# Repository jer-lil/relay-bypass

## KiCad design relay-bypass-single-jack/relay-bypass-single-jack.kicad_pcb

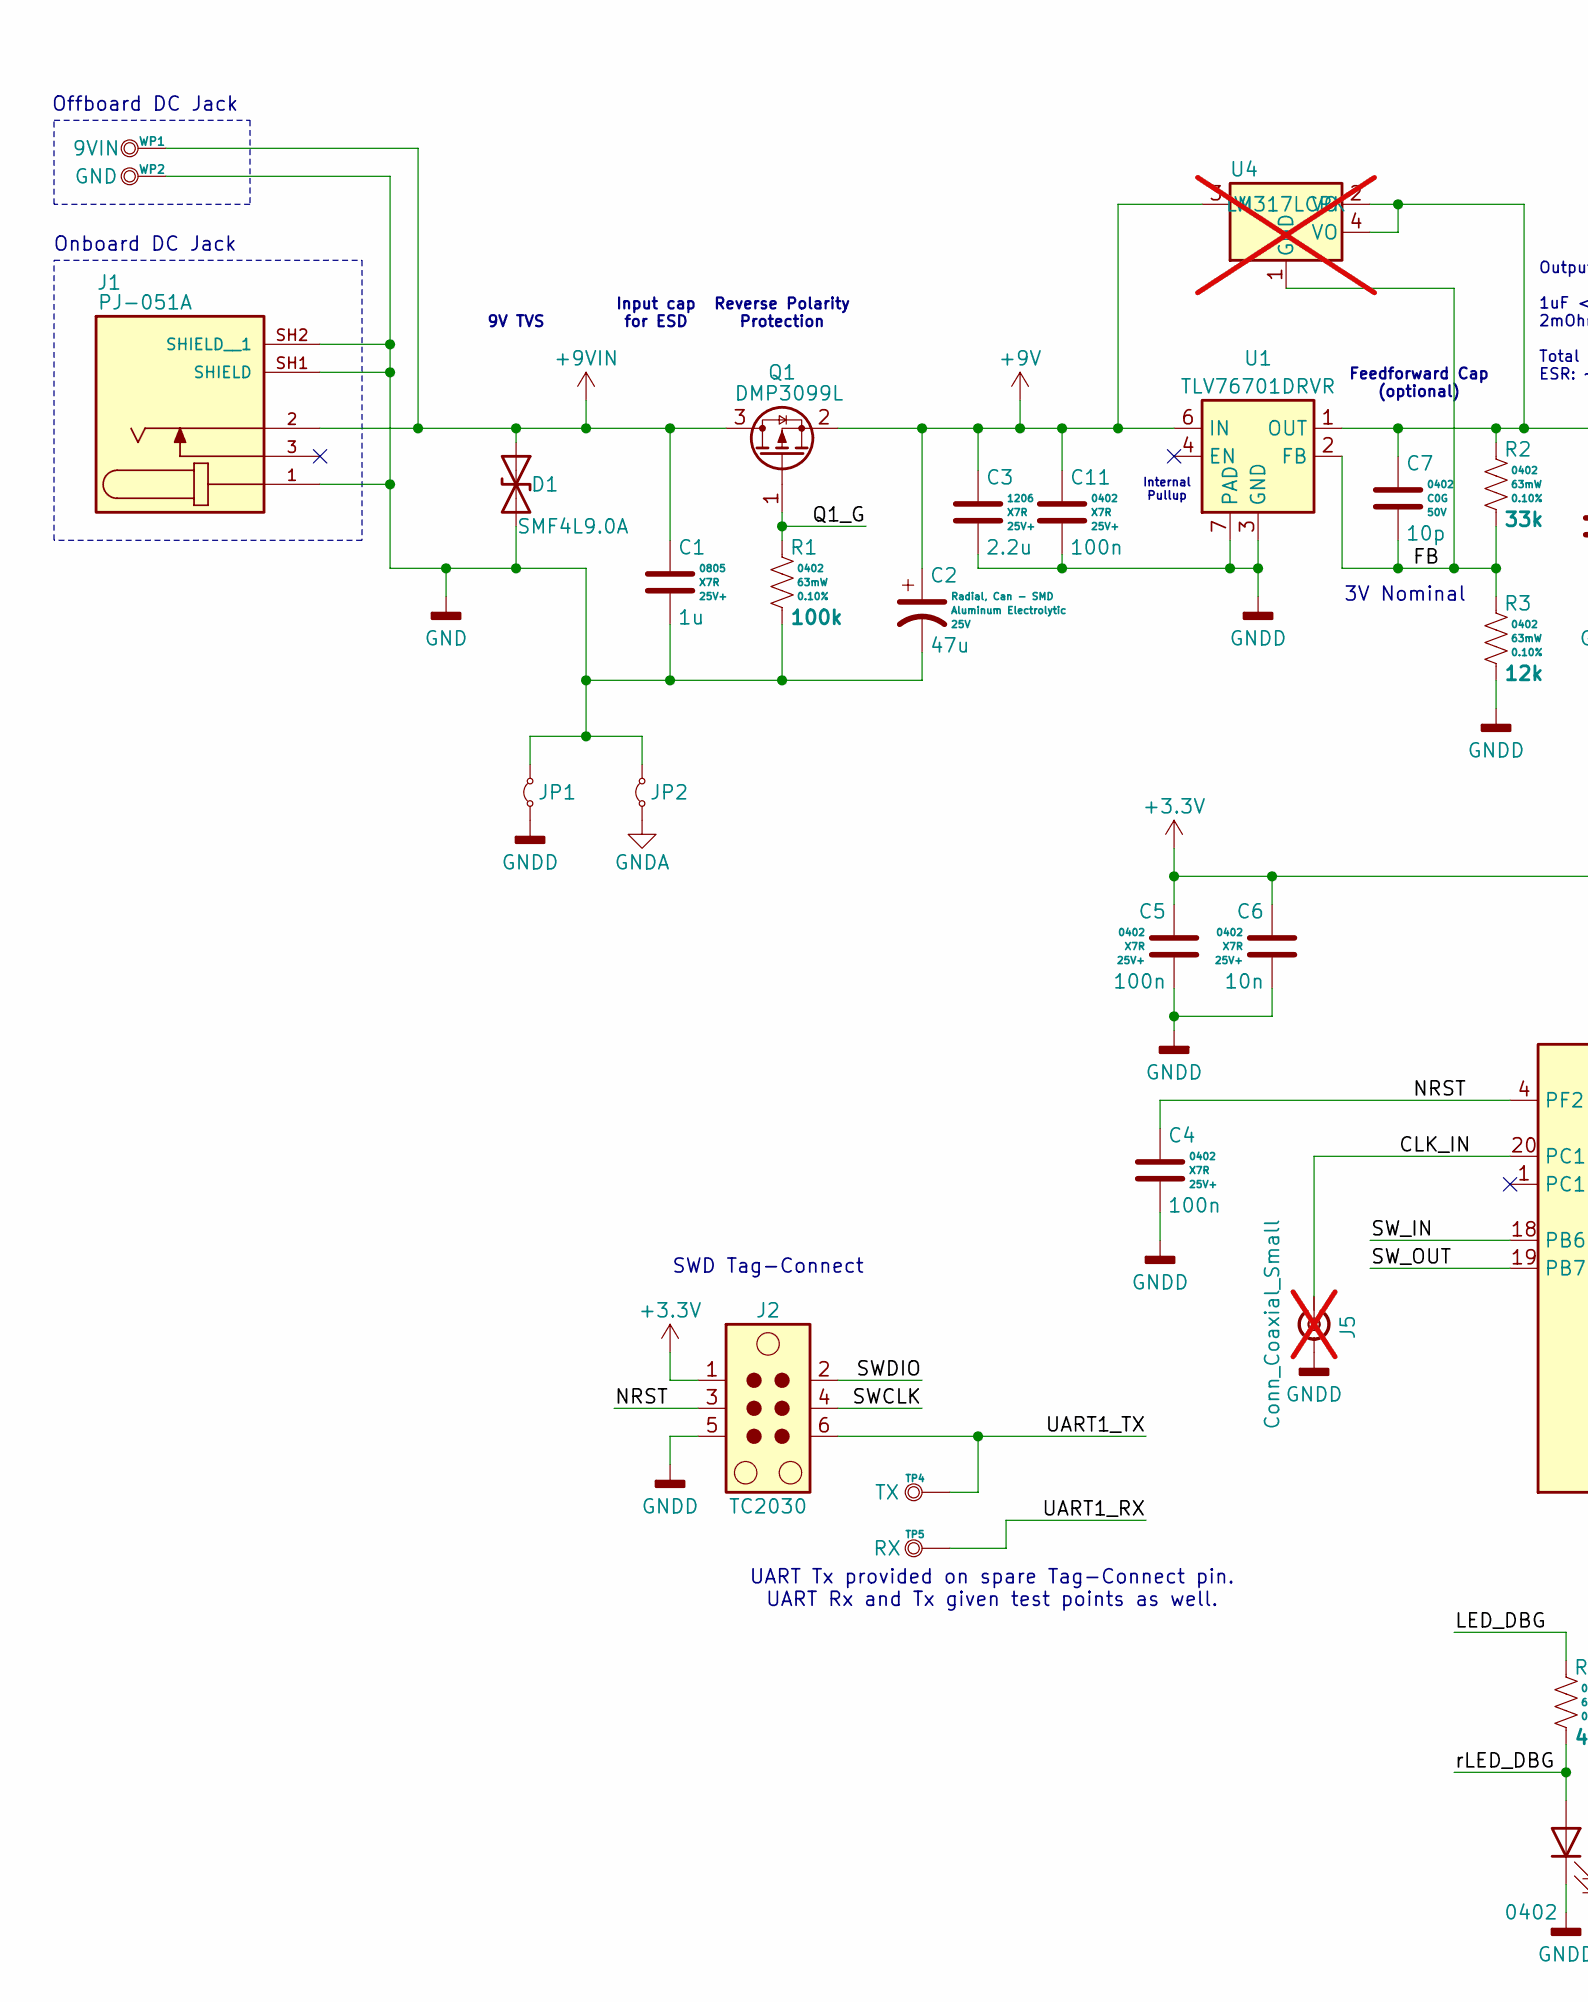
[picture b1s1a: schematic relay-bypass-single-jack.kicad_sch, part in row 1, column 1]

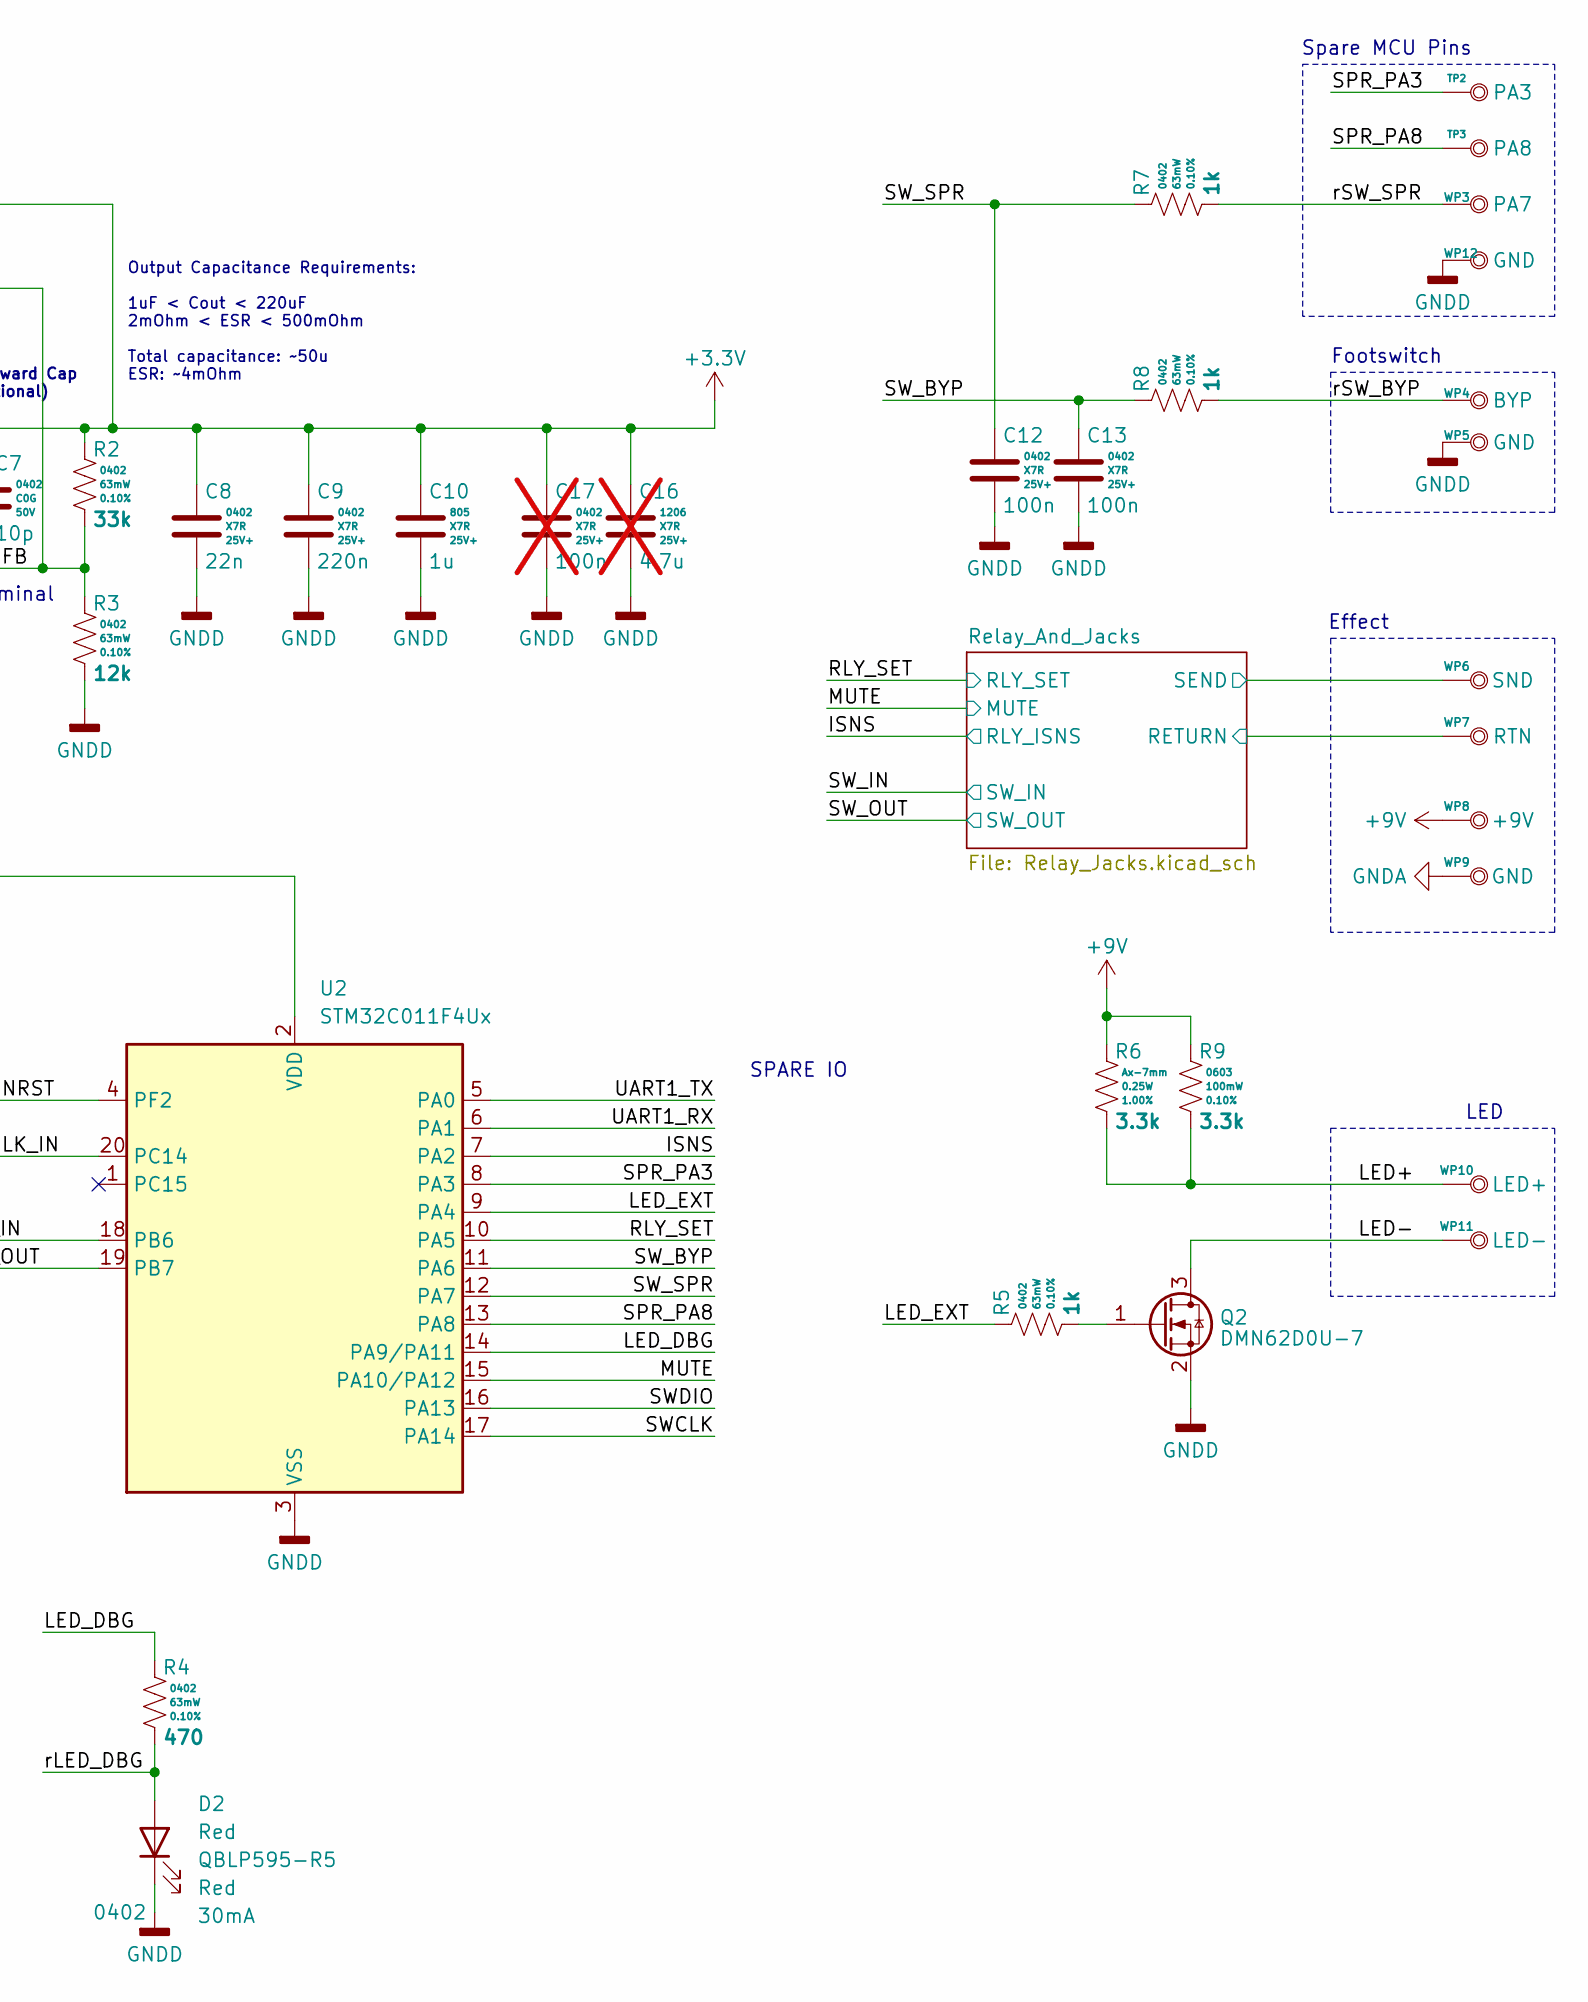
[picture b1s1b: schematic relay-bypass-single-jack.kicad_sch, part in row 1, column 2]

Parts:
C1, C10: 1u; C_0805_2012Metric; Voltage 25V+; Tolerance 10%; MPN C0805C105K3RACTU
C2: 47u; CP_Elec_6.3x5.8; Voltage 25V; Tolerance +/-20%; MPN EEE-FK1E470P
C3: 2.2u; C_1206_3216Metric; Voltage 25V+; Tolerance 10%; MPN C1206C225K3RACTU
C4, C5, C11, C12, C13: 100n; C_0402_1005Metric; Voltage 25V+; Tolerance 10%; MPN C0402C104K3RACTU
C6: 10n; C_0402_1005Metric; Voltage 25V+; Tolerance 10%; MPN C0402C103K3RACTU
C7: 10p; C_0402_1005Metric; Voltage 50V; Tolerance +/-2%; MPN GRM1555C1H100GA01D
C8: 22n; C_0402_1005Metric; Voltage 25V+; Tolerance 10%; MPN C0402C223K3RACTU
C9: 220n; C_0402_1005Metric; Voltage 25V+; Tolerance 10%; MPN C0402C224K3RACTU
C16: 4.7u; C_1206_3216Metric; Voltage 25V+; Tolerance 10%; MPN C1206C475K3RACTU; not fitted
C17: 100n; C_0402_1005Metric; Voltage 25V+; Tolerance 10%; MPN C0402C104K3RACTU; not fitted
D1: SMF4L9.0A; D_SOD-123F; MPN SMF4L9.0A
D2: Red; LED_0402_1005Metric; MPN QBLP595-R5
J1: 3; BarrelJack_CUI_PJ-051A; PARTREV 1.06
J2: TC2030; Tag-Connect_TC2030-IDC-NL_2x03_P1.27mm_Vertical
J5: Conn_Coaxial_Small; U.FL_Hirose_U.FL-R-SMT-1_Vertical; not fitted
JP1, JP2: Jumper_2_Small_Bridged; SolderJumper-2_P1.3mm_Bridged2Bar_Pad1.0x1.5mm
Q1: DMP3099L; SOT-23; MPN DMP3099L
Q2: DMN62D0U-7; SOT-23; MPN DMN62D0U-7
R1: 100k; R_0402_1005Metric; Tolerance 0.10%; Voltage 50V; MPN RT0402BRD07100KL
R2: 33k; R_0402_1005Metric; Tolerance 0.10%; Voltage 50V; MPN RT0402BRD0733KL
R3: 12k; R_0402_1005Metric; Tolerance 0.10%; Voltage 50V; MPN RT0402BRD0712KL
R4: 470; R_0402_1005Metric; Tolerance 0.10%; Voltage 50V; MPN RT0402BRD07470RL
R5, R7, R8: 1k; R_0402_1005Metric; Tolerance 0.10%; Voltage 50V; MPN RT0402BRD071KL
R6: 3.3k; R_Axial_DIN0207_L6.3mm_D2.5mm_P7.5mm_Horizontal; Tolerance 1.00%; Voltage 250V; MPN MFR-25FBF52-3K3
R9: 3.3k; R_0603_1608Metric; Tolerance 0.10%; Voltage 75V; MPN RT0603BRD073K3L
TP2: PA3; TestPoint_PTH_H1.02mm_NoOutline
TP3: PA8; TestPoint_PTH_H1.02mm_NoOutline
TP4: TX; TestPoint_PTH_H1.02mm_NoOutline
TP5: RX; TestPoint_PTH_H1.02mm_NoOutline
U1: TLV76701DRVR; WSON-6-1EP_2x2mm_P0.65mm_EP1x1.6mm; Voltage ADJ; MPN TLV76701DRVR
U2: STM32C011F4Ux; ST_UFQFPN-20_3x3mm_P0.5mm
U4: LM317LCPK; SOT-223; Voltage ADJ; MPN LM317LCPK; not fitted
WP1: 9VIN; WirePad_H0.95mm_22-24AWG
WP2, WP5, WP9, WP12: GND; WirePad_H0.95mm_22-24AWG
WP3: PA7; WirePad_H0.95mm_22-24AWG
WP4: BYP; WirePad_H0.95mm_22-24AWG
WP6: SND; WirePad_H0.95mm_22-24AWG
WP7: RTN; WirePad_H0.95mm_22-24AWG
WP8: +9V; WirePad_H0.95mm_22-24AWG
WP10: LED+; WirePad_H0.95mm_22-24AWG
WP11: LED-; WirePad_H0.95mm_22-24AWG

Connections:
+3.3V: C5.1, C6.1, C7.1, C8.1, C9.1, C10.1, C16.1, C17.1, J2.1, R2.1, U1.1 (OUT), U2.2 (VDD), U4.2 (VO), U4.4 (VO); also elsewhere on the board
+9V: C2.1, C3.1, C11.1, Q1.2 (S), R6.1, R9.1, U1.6 (IN), U4.3 (VI), WP8.1; also elsewhere on the board
+9VIN: C1.1, D1.1 (A1), J1.2, Q1.3 (D), WP1.1
/CLK_IN: J5.1 (In), U2.20 (PC14)
/FB: C7.2, R2.2, R3.1, U1.2 (FB), U4.1 (GND)
/ISNS: U2.7 (PA2); also elsewhere on the board
/LED+: R6.2, R9.2, WP10.1
/LED-: Q2.3 (D), WP11.1
/LED_DBG: R4.1, U2.14 (PA9/PA11)
/LED_EXT: R5.1, U2.9 (PA4)
/MUTE: U2.15 (PA10/PA12); also elsewhere on the board
/NRST: C4.1, J2.3, U2.4 (PF2)
/Q1_G: Q1.1 (G), R1.1
/RLY_SET: U2.10 (PA5); also elsewhere on the board
/Relay_And_Jacks/RETURN: WP7.1; also elsewhere on the board
/Relay_And_Jacks/SEND: WP6.1; also elsewhere on the board
/SPR_PA3: TP2.1, U2.8 (PA3)
/SPR_PA8: TP3.1, U2.13 (PA8)
/SWCLK: J2.4, U2.17 (PA14)
/SWDIO: J2.2, U2.16 (PA13)
/SW_BYP: C13.1, R8.1, U2.11 (PA6)
/SW_IN: U2.18 (PB6); also elsewhere on the board
/SW_OUT: U2.19 (PB7); also elsewhere on the board
/SW_SPR: C12.1, R7.1, U2.12 (PA7)
/UART1_RX: TP5.1, U2.6 (PA1)
/UART1_TX: J2.6, TP4.1, U2.5 (PA0)
/rLED_DBG: D2.2 (A), R4.2
/rSW_BYP: R8.2, WP4.1
/rSW_SPR: R7.2, WP3.1
GND: C1.2, C2.2, D1.2 (A2), J1.1, J1.SH1 (SHIELD), J1.SH2 (SHIELD__1), JP1.2 (B), JP2.2 (B), R1.2, WP2.1
GNDA: JP2.1 (A), WP9.1; also elsewhere on the board
GNDD: C3.2, C4.2, C5.2, C6.2, C8.2, C9.2, C10.2, C11.2, C12.2, C13.2, C16.2, C17.2, D2.1 (K), J2.5, J5.2 (Ext), JP1.1 (A), Q2.2 (S), R3.2, U1.3 (GND), U1.5 (GND), U1.7 (PAD), U2.3 (VSS), WP5.1, WP12.1; also elsewhere on the board
unnamed: Q2.1 (G), R5.2

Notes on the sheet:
Input cap for ESD
SWD Tag-Connect
Spare MCU Pins
Effect
9V TVS
Reverse Polarity Protection
3V Nominal
Output Capacitance Requirements: 1uF < Cout < 220uF 2mOhm < ESR < 500mOhm Total capacitance: ~50u ESR: ~4mOhm
LED
Footswitch
Feedforward Cap (optional)
SPARE IO
Onboard DC Jack
Internal Pullup
UART Tx provided on spare Tag-Connect pin. UART Rx and Tx given test points as well.
Offboard DC Jack

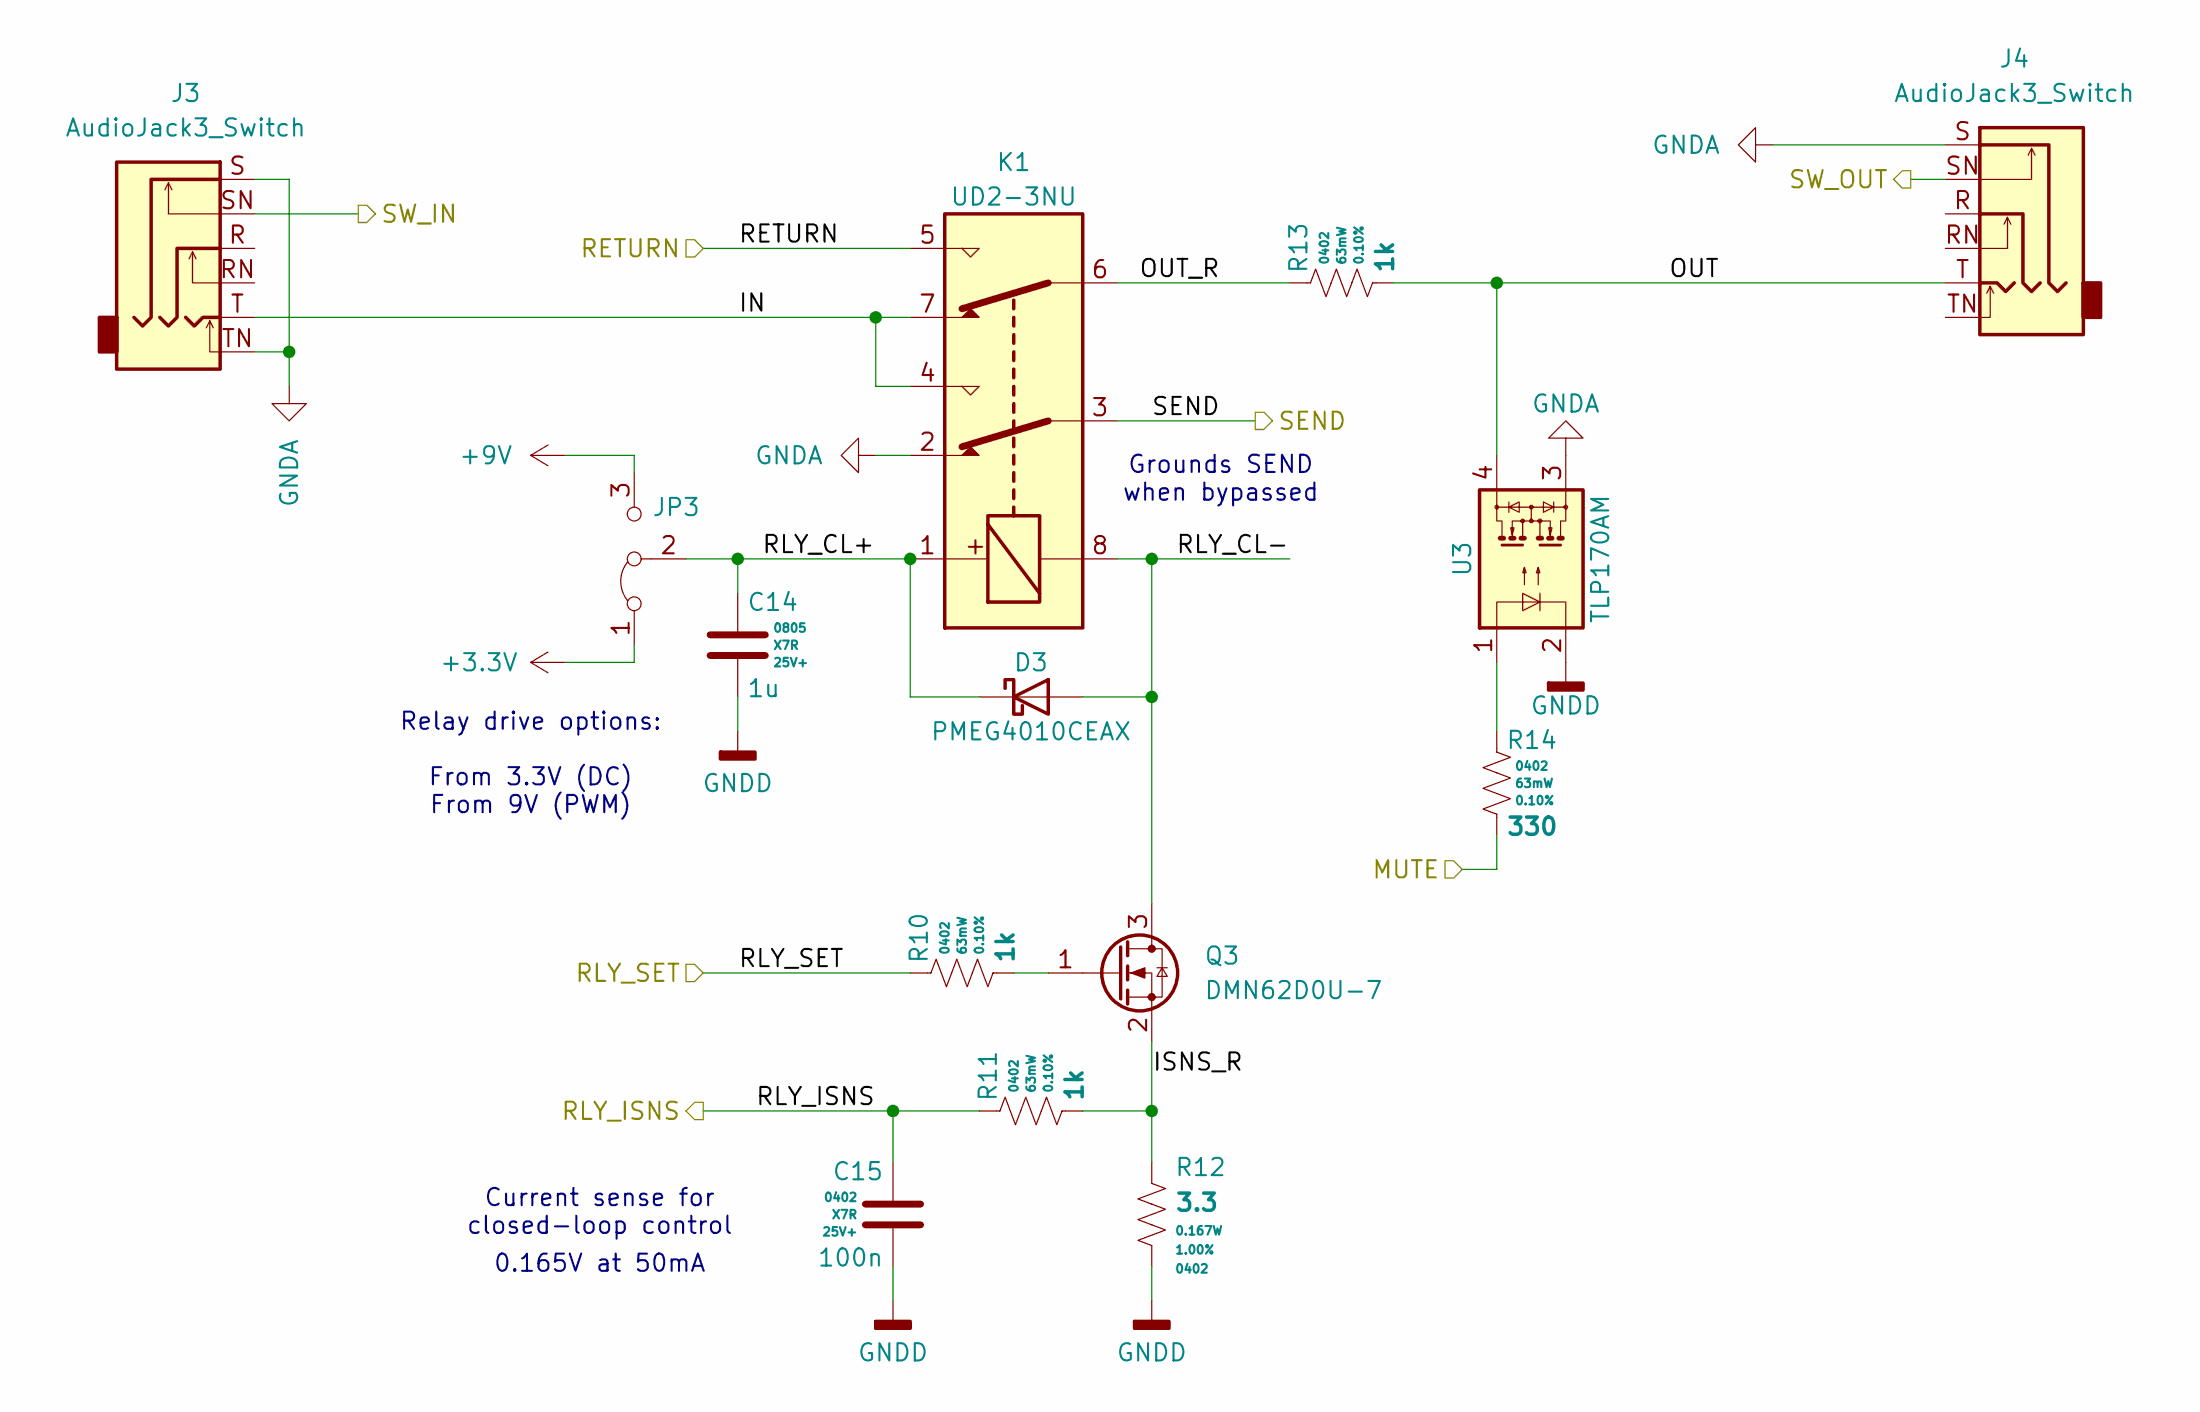
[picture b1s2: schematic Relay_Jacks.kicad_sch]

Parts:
C14: 1u; C_0805_2012Metric; Voltage 25V+; Tolerance 10%; MPN C0805C105K3RACTU
C15: 100n; C_0402_1005Metric; Voltage 25V+; Tolerance 10%; MPN C0402C104K3RACTU
D3: PMEG4010CEAX; D_SOD-323; Voltage 840 mV @ 1 A; MPN PMEG4010CEAX
J3, J4: AudioJack3_Switch; Jack_6.35mm_Neutrik_NMJ6HCD2_LARGE_SLOTS
JP3: Jumper_3_Bridged12; SolderJumper-3_P1.3mm_Bridged12_Pad1.0x1.5mm
K1: IM05JR; UD23NU; MPN UD2-3NU
Q3: DMN62D0U-7; SOT-23; MPN DMN62D0U-7
R10, R11, R13: 1k; R_0402_1005Metric; Tolerance 0.10%; Voltage 50V; MPN RT0402BRD071KL
R12: 3.3; R_0402_1005Metric; Tolerance 1.00%; Voltage 50V; MPN RL0510S-3R3-F
R14: 330; R_0402_1005Metric; Tolerance 0.10%; Voltage 50V; MPN RT0402BRD07330RL
U3: TLP170AM; SO-4_4.4x3.9mm_P2.54mm; MPN TLP170AM

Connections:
+3.3V: JP3.1 (A); also elsewhere on the board
+9V: JP3.3 (B); also elsewhere on the board
/ISNS: C15.1, R11.1; also elsewhere on the board
/MUTE: R14.2; also elsewhere on the board
/RLY_SET: R10.1; also elsewhere on the board
/Relay_And_Jacks/IN: J3.T, K1.4, K1.7
/Relay_And_Jacks/ISNS_R: Q3.2 (S), R11.2, R12.1
/Relay_And_Jacks/OUT: J4.T, R13.2, U3.4
/Relay_And_Jacks/OUT_R: K1.6, R13.1
/Relay_And_Jacks/RETURN: K1.5; also elsewhere on the board
/Relay_And_Jacks/RLY_CL+: C14.1, D3.1 (K), JP3.2 (C), K1.1
/Relay_And_Jacks/RLY_CL-: D3.2 (A), K1.8, Q3.3 (D)
/Relay_And_Jacks/SEND: K1.3; also elsewhere on the board
/SW_IN: J3.SN; also elsewhere on the board
/SW_OUT: J4.SN; also elsewhere on the board
GNDA: J3.S, J3.TN, J4.S, K1.2, U3.3; also elsewhere on the board
GNDD: C14.2, C15.2, R12.2, U3.2; also elsewhere on the board
unnamed: Q3.1 (G), R10.2
unnamed: R14.1, U3.1

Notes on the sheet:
Current sense for closed-loop control
Grounds SEND when bypassed
Relay drive options: From 3.3V (DC) From 9V (PWM)
0.165V at 50mA

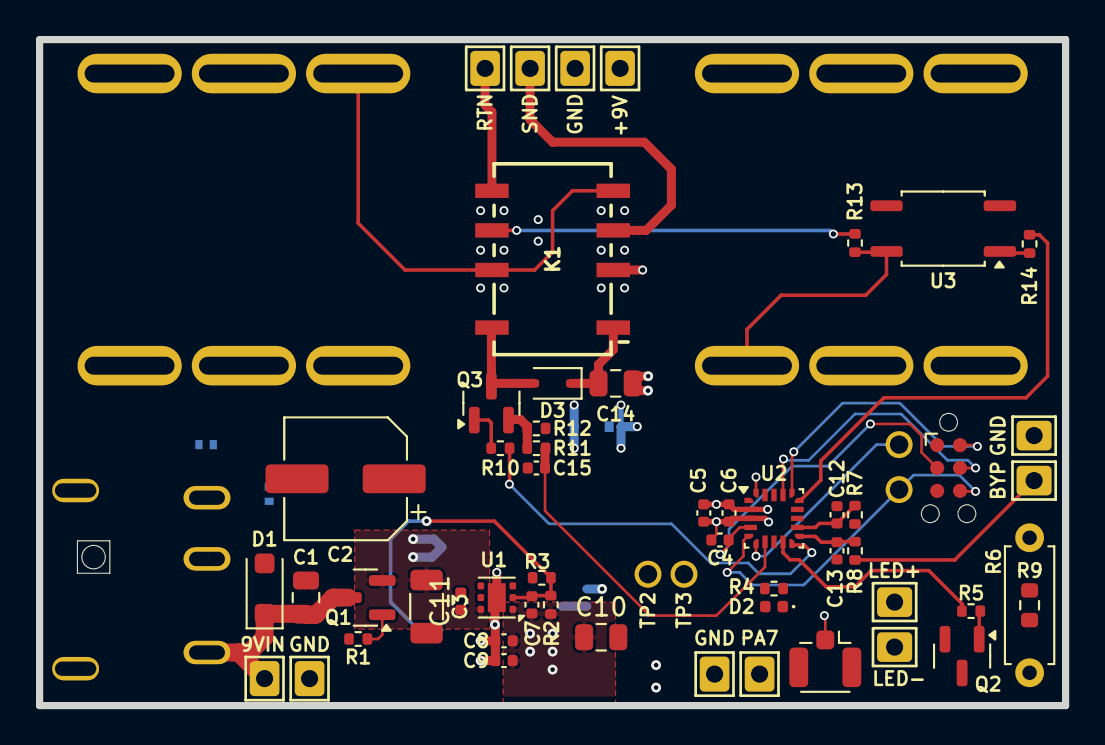
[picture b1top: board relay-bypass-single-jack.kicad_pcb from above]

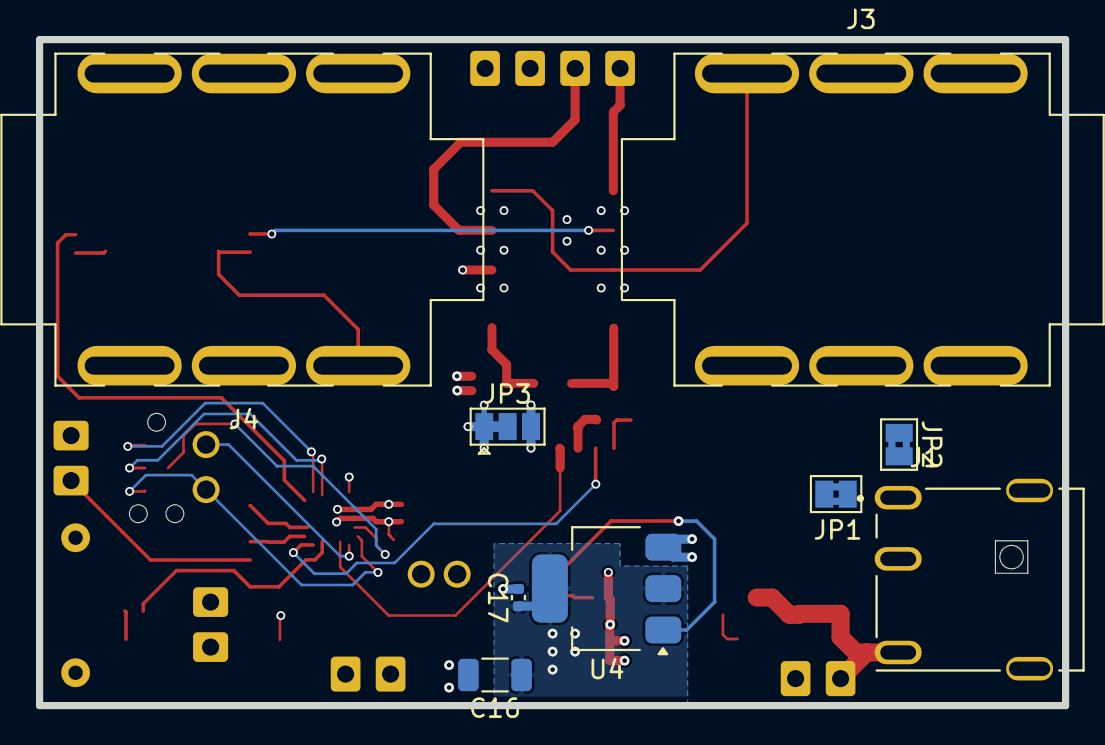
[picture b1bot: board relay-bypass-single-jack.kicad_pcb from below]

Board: 4 copper layers, 57.0 x 37.0 mm, 66 parts (9 on the bottom side), 41 nets.
